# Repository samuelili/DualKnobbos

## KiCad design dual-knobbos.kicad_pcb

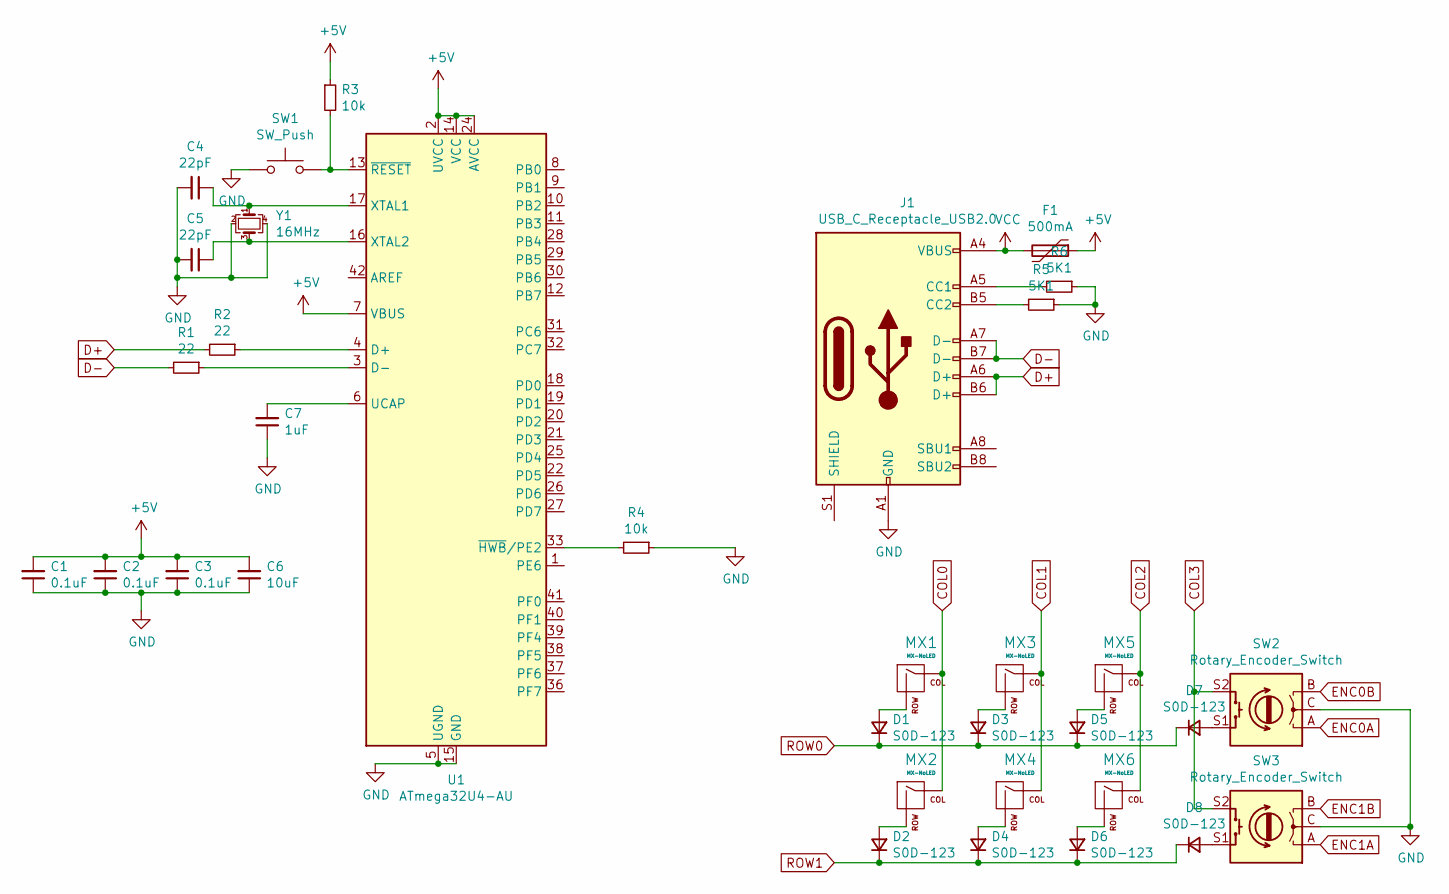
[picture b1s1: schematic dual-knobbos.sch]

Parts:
C1, C2, C3: 0.1uF; C_0805_2012Metric
C4, C5: 22pF; C_0805_2012Metric
C6: 10uF; C_0805_2012Metric
C7: 1uF; C_0805_2012Metric
D1, D2, D3, D4, D5, D6, D7, D8: S0D-123; D_DO-35_SOD27_P5.08mm_Vertical_AnodeUp
F1: 500mA; Fuse_1206_3216Metric
J1: USB_C_Receptacle_USB2.0; USB_C_GCT_USB4085
MX1, MX2, MX3, MX4, MX5, MX6: MX-NoLED; MX-1U-NoLED
R1, R2: 22; R_0805_2012Metric
R3, R4: 10k; R_0805_2012Metric
R5, R6: 5K1; R_0805_2012Metric
SW1: SW_Push; SKQG-1155865
SW2, SW3: Rotary_Encoder_Switch; RotaryEncoder_Alps_EC11E-Switch_Vertical_H20mm
U1: ATmega32U4-AU; TQFP-44_10x10mm_P0.8mm
Y1: 16MHz; Crystal_SMD_3225-4Pin_3.2x2.5mm

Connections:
+5V: C1.2, C2.2, C3.2, C6.2, F1.1, R3.1, U1.2 (UVCC), U1.7 (VBUS), U1.14 (VCC), U1.24 (AVCC), U1.34 (VCC), U1.44 (AVCC)
COL0: MX1.1 (COL), MX2.1 (COL), U1.39 (PF4)
COL1: MX3.1 (COL), MX4.1 (COL), U1.40 (PF1)
COL2: MX5.1 (COL), MX6.1 (COL), U1.41 (PF0)
COL3: SW2.S2, SW3.S2, U1.26 (PD6), U1.38 (PF5)
D+: J1.A6 (D+), J1.B6 (D+), R2.2
D-: J1.A7 (D-), J1.B7 (D-), R1.2
ENC0A: SW2.A, U1.27 (PD7)
ENC0B: SW2.B, U1.28 (PB4)
ENC1A: SW3.A, U1.29 (PB5)
ENC1B: SW3.B, U1.30 (PB6)
GND: C1.1, C2.1, C3.1, C4.2, C5.2, C6.1, C7.1, J1.A1 (GND), J1.A12 (GND), J1.B1 (GND), J1.B12 (GND), R4.1, R5.1, R6.1, SW1.1, SW2.C, SW3.C, U1.5 (UGND), U1.15 (GND), U1.23 (GND), U1.35 (GND), U1.43 (GND), Y1.2, Y1.4
unnamed: C4.1, U1.17 (XTAL1), Y1.1
unnamed: C5.1, U1.16 (XTAL2), Y1.3
unnamed: C7.2, U1.6 (UCAP)
unnamed: D1.2 (A), MX1.2 (ROW)
unnamed: D2.2 (A), MX2.2 (ROW)
unnamed: D3.2 (A), MX3.2 (ROW)
unnamed: D4.2 (A), MX4.2 (ROW)
unnamed: D5.2 (A), MX5.2 (ROW)
unnamed: D6.2 (A), MX6.2 (ROW)
unnamed: D7.2 (A), SW2.S1
unnamed: D8.2 (A), SW3.S1
unnamed: J1.A5 (CC1), R6.2
unnamed: J1.B5 (CC2), R5.2
unnamed: R1.1, U1.3 (D-)
unnamed: R2.1, U1.4 (D+)
unnamed: R3.2, SW1.2, U1.13 (~RESET)
unnamed: R4.2, U1.33 (~HWB~/PE2)
ROW0: D1.1 (K), D3.1 (K), D5.1 (K), D7.1 (K)
ROW1: D2.1 (K), D4.1 (K), D6.1 (K), D8.1 (K)
VCC: F1.2, J1.A4 (VBUS), J1.A9 (VBUS), J1.B4 (VBUS), J1.B9 (VBUS)

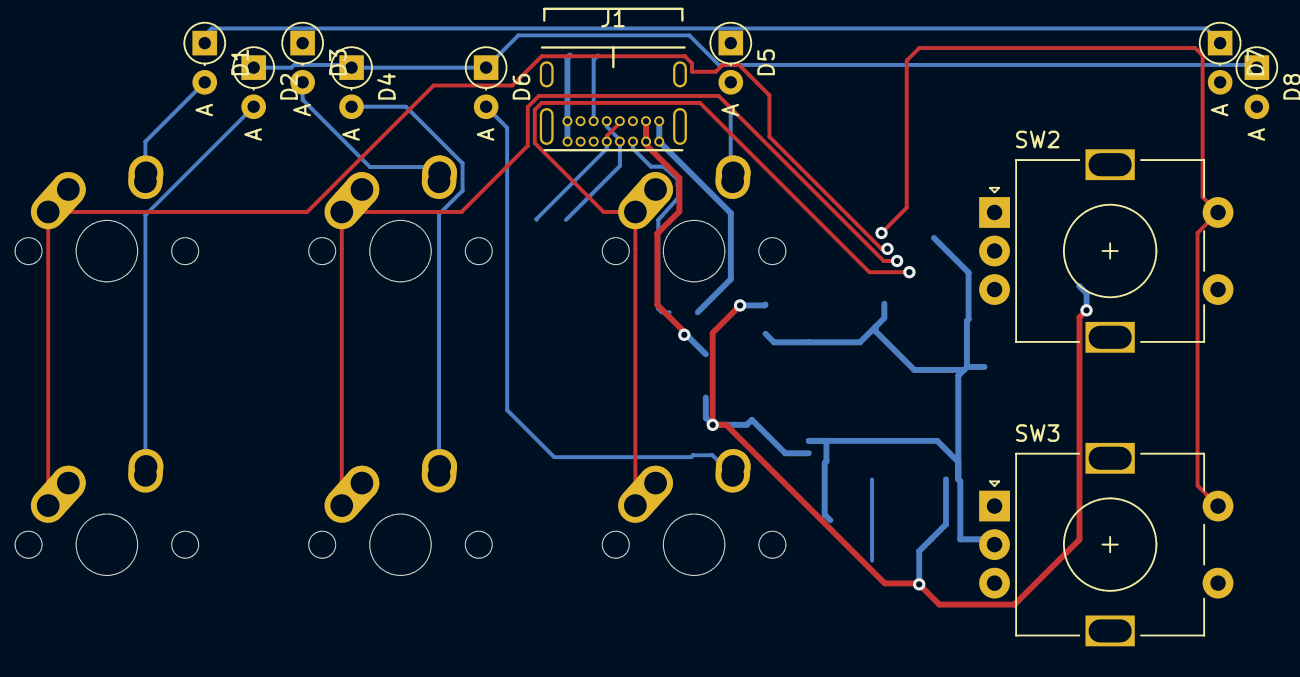
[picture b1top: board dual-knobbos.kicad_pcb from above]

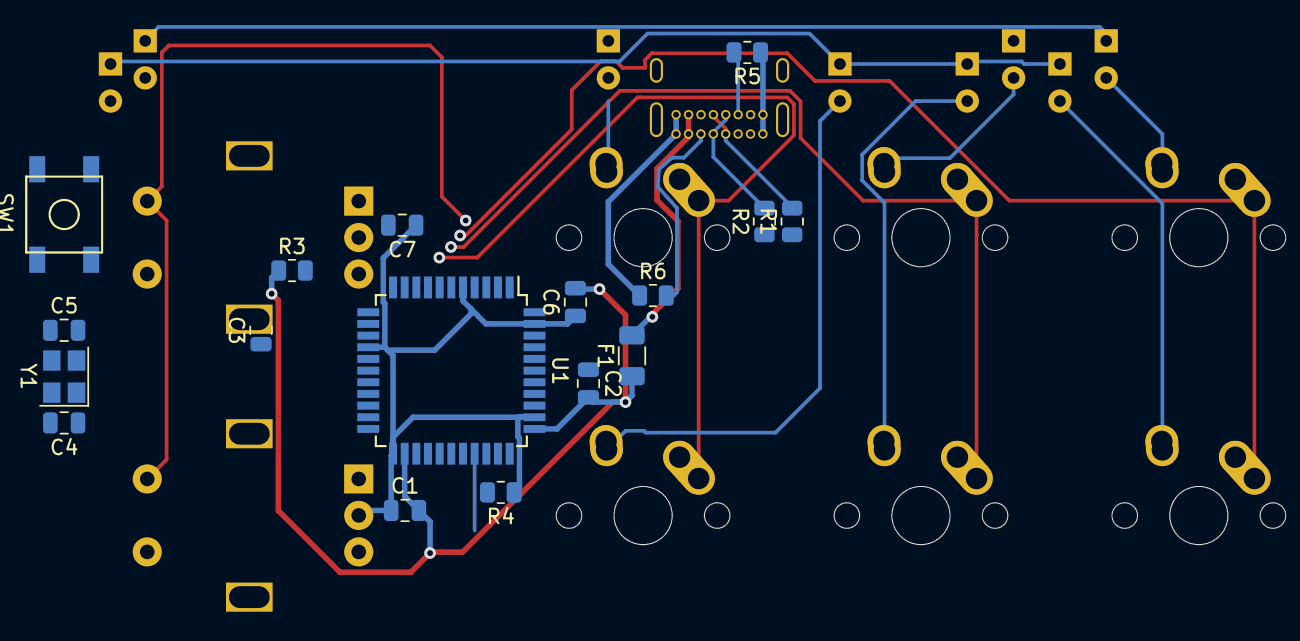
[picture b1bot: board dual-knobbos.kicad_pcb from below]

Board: 2 copper layers, 34 parts (17 on the bottom side), 32 nets.

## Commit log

2021-03-31 added git submodules
2021-03-31 added schematics
2021-03-31 finished schematic
2021-04-01 uh stuff
2021-04-02 mid commit
2021-06-11 some commit idk
